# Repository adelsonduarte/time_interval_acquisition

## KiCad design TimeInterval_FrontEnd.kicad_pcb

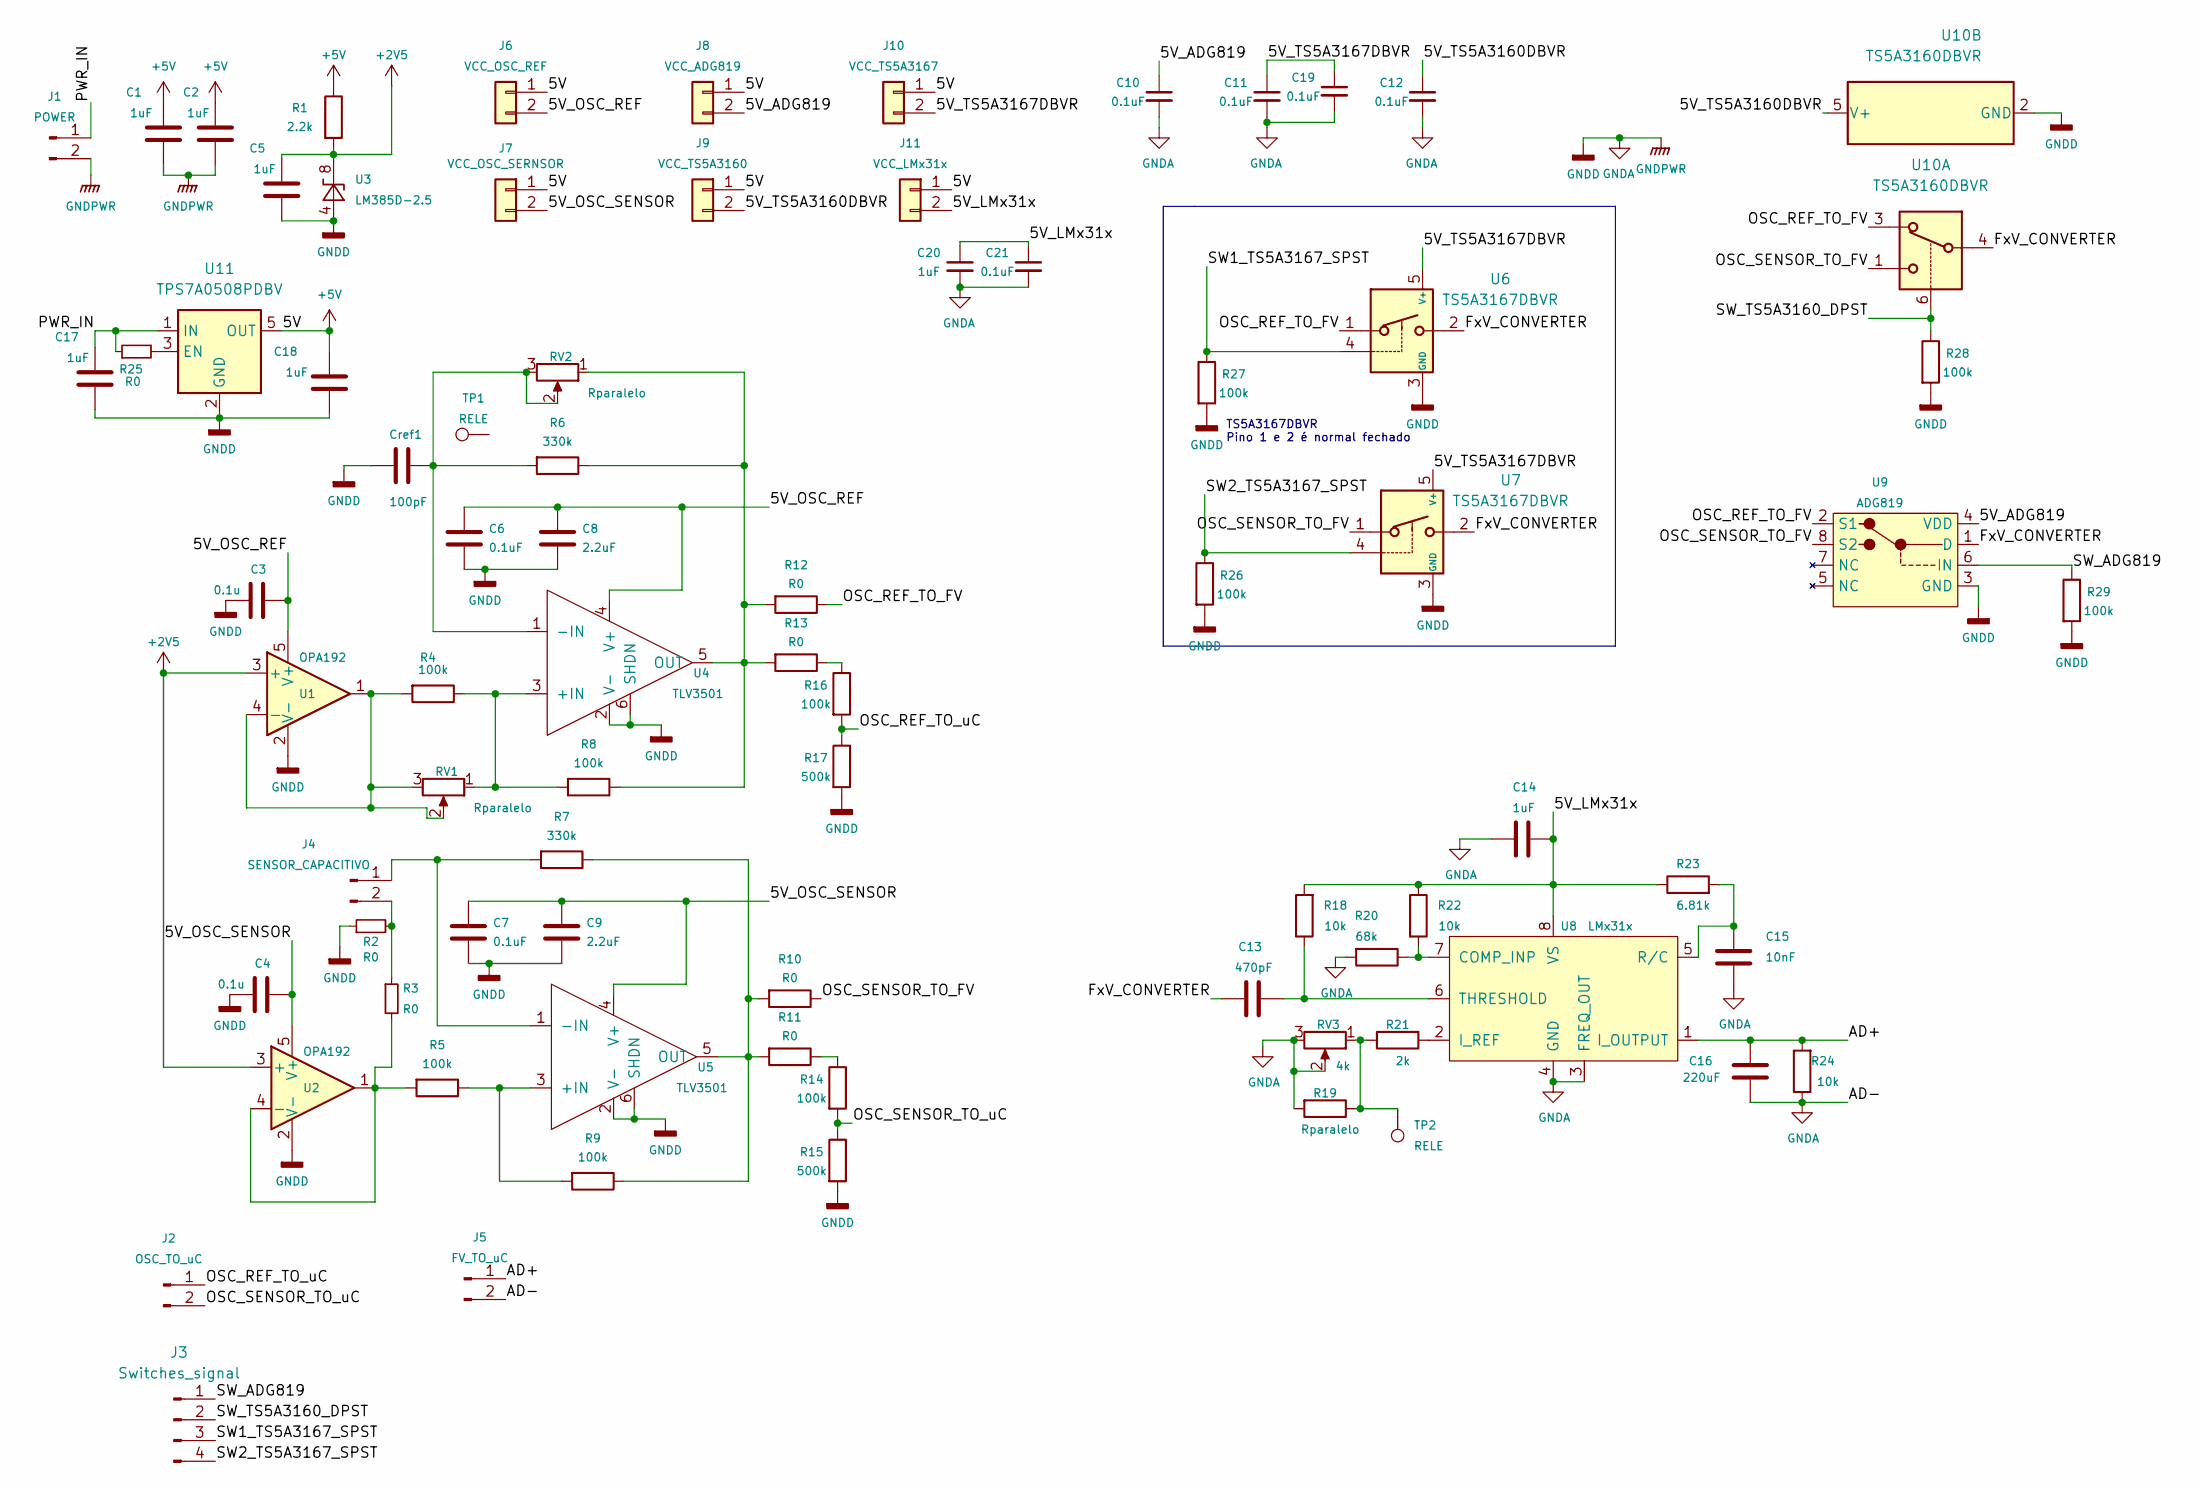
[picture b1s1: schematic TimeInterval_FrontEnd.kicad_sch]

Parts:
C1, C2, C5, C14, C17, C18, C20: 1uF; C_1206_3216Metric_Pad1.33x1.80mm_HandSolder
C3, C4: 0.1u; C_1206_3216Metric_Pad1.33x1.80mm_HandSolder
C6, C7, C10, C11, C12, C19, C21: 0.1uF; C_1206_3216Metric_Pad1.33x1.80mm_HandSolder
C8, C9: 2.2uF; C_1206_3216Metric_Pad1.33x1.80mm_HandSolder
C13: 470pF; C_1206_3216Metric_Pad1.33x1.80mm_HandSolder
C15: 10nF; C_1206_3216Metric_Pad1.33x1.80mm_HandSolder
C16: 220uF; CP_Elec_10x14.3
Cref1: 100pF; C_1206_3216Metric_Pad1.33x1.80mm_HandSolder
J1: POWER; Molex_KK-254_AE-6410-02A_1x02_P2.54mm_Vertical
J2: OSC_TO_uC; Molex_KK-254_AE-6410-02A_1x02_P2.54mm_Vertical
J3: Switches_signal; Molex_KK-254_AE-6410-04A_1x04_P2.54mm_Vertical
J4: SENSOR_CAPACITIVO; Molex_KK-254_AE-6410-02A_1x02_P2.54mm_Vertical
J5: FV_TO_uC; Molex_KK-254_AE-6410-02A_1x02_P2.54mm_Vertical
J6: VCC_OSC_REF; PinHeader_1x02_P2.54mm_Vertical
J7: VCC_OSC_SERNSOR; PinHeader_1x02_P2.54mm_Vertical
J8: VCC_ADG819; PinHeader_1x02_P2.54mm_Vertical
J9: VCC_TS5A3160; PinHeader_1x02_P2.54mm_Vertical
J10: VCC_TS5A3167; PinHeader_1x02_P2.54mm_Vertical
J11: VCC_LMx31x; PinHeader_1x02_P2.54mm_Vertical
R1: 2.2k; R_1206_3216Metric_Pad1.30x1.75mm_HandSolder
R2, R3, R10, R11, R12, R13, R25: R0; R_1206_3216Metric_Pad1.30x1.75mm_HandSolder
R4, R5, R8, R9, R14, R16, R26, R27, R28, R29: 100k; R_1206_3216Metric_Pad1.30x1.75mm_HandSolder
R6, R7: 330k; R_1206_3216Metric_Pad1.30x1.75mm_HandSolder
R15, R17: 500k; R_1206_3216Metric_Pad1.30x1.75mm_HandSolder
R18, R22, R24: 10k; R_1206_3216Metric_Pad1.30x1.75mm_HandSolder
R19: Rparalelo; R_1206_3216Metric_Pad1.30x1.75mm_HandSolder
R20: 68k; R_1206_3216Metric_Pad1.30x1.75mm_HandSolder
R21: 2k; R_1206_3216Metric_Pad1.30x1.75mm_HandSolder
R23: 6.81k; R_1206_3216Metric_Pad1.30x1.75mm_HandSolder
RV1, RV2: Rparalelo; Potentiometer_Bourns_3296W_Vertical
RV3: 4k; Potentiometer_Bourns_3296W_Vertical
TP1, TP2: RELE; TestPoint_Pad_1.0x1.0mm
U1, U2: OPA192; SOT-23-5_HandSoldering
U3: LM385D-2.5; SOIC-8_3.9x4.9mm_P1.27mm
U4, U5: TLV3501; SOT-23-6_Handsoldering
U6, U7: TS5A3167DBVR; SOT-23-5
U8: LMx31x; DIP-8_W7.62mm
U9: ADG819; MSOP-8_3x3mm_P0.65mm
U10: TS5A3160DBVR; SOT-23-6
U11: TPS7A0508PDBV; SOT-23-5

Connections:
+2V5: C5.2, R1.2, U1.3 (+), U2.3 (+), U3.8 (K)
+5V: C1.2, C2.2, C18.2, J6.1, J7.1, J8.1, J9.1, J10.1, J11.1, R1.1, U11.5 (OUT)
/5V_ADG819: C10.1, J8.2, U9.4 (VDD)
/5V_LMx31x: C14.1, C20.1, C21.1, J11.2, R18.2, R22.1, R23.1, U8.8 (VS)
/5V_OSC_REF: C3.2, C6.1, C8.1, J6.2, U1.5 (V+), U4.4 (V+)
/5V_OSC_SENSOR: C4.2, C7.1, C9.1, J7.2, U2.5 (V+), U5.4 (V+)
/5V_TS5A3160DBVR: C12.1, J9.2, U10.5 (V+)
/5V_TS5A3167DBVR: C11.1, C19.1, J10.2, U6.5 (V+), U7.5 (V+)
/AD+: C16.1, J5.1, R24.2, U8.1 (I_OUTPUT)
/FxV_CONVERTER: C13.1, U6.2, U7.2, U9.1 (D), U10.4
/OSC_REF_TO_FV: R12.1, U6.1, U9.2 (S1), U10.3
/OSC_REF_TO_uC: J2.1, R16.2, R17.1
/OSC_SENSOR_TO_FV: R10.1, U7.1, U9.8 (S2), U10.1
/OSC_SENSOR_TO_uC: J2.2, R14.2, R15.1
/PWR_IN: C17.2, J1.1, R25.1, U11.1 (IN)
/SW1_TS5A3167_SPST: J3.3, R27.1, U6.4
/SW2_TS5A3167_SPST: J3.4, R26.1, U7.4
/SW_ADG819: J3.1, R29.1, U9.6 (IN)
/SW_TS5A3160_DPST: J3.2, R28.1, U10.6
GNDA: C1.1, C2.1, C3.1, C4.1, C5.1, C6.2, C7.2, C8.2, C9.2, C10.2, C11.2, C12.2, C14.2, C15.2, C16.2, C17.1, C18.1, C19.2, C20.2, C21.2, Cref1.1, J1.2, J5.2, R2.1, R15.2, R17.2, R19.2, R20.2, R24.1, R26.2, R27.2, R28.2, R29.2, RV3.2, RV3.3, U1.2 (V-), U2.2 (V-), U3.4 (A), U4.2 (V-), U4.6 (SHDN), U5.2 (V-), U5.6 (SHDN), U6.3 (GND), U7.3 (GND), U8.3 (FREQ_OUT), U8.4 (GND), U9.3 (GND), U10.2 (GND), U11.2 (GND)
unnamed: C13.2, R18.1, U8.6 (THRESHOLD)
unnamed: C15.1, R23.2, U8.5 (R/C)
unnamed: Cref1.2, R6.2, RV2.2, RV2.3, U4.1 (-IN)
unnamed: J4.1, R7.2, U5.1 (-IN)
unnamed: J4.2, R2.2, R3.1
unnamed: R3.2, R5.2, U2.1, U2.4 (-)
unnamed: R4.1, R8.2, RV1.1, U4.3 (+IN)
unnamed: R4.2, RV1.2, RV1.3, U1.1, U1.4 (-)
unnamed: R5.1, R9.2, U5.3 (+IN)
unnamed: R7.1, R9.1, R10.2, R11.2, U5.5 (OUT)
unnamed: R11.1, R14.1
unnamed: R6.1, R8.1, R12.2, R13.2, RV2.1, U4.5 (OUT)
unnamed: R13.1, R16.1
unnamed: R19.1, R21.2, RV3.1, TP2.1
unnamed: R20.1, R22.2, U8.7 (COMP_INP)
unnamed: R21.1, U8.2 (I_REF)
unnamed: R25.2, U11.3 (EN)

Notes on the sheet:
TS5A3167DBVR Pino 1 e 2 é normal fechado

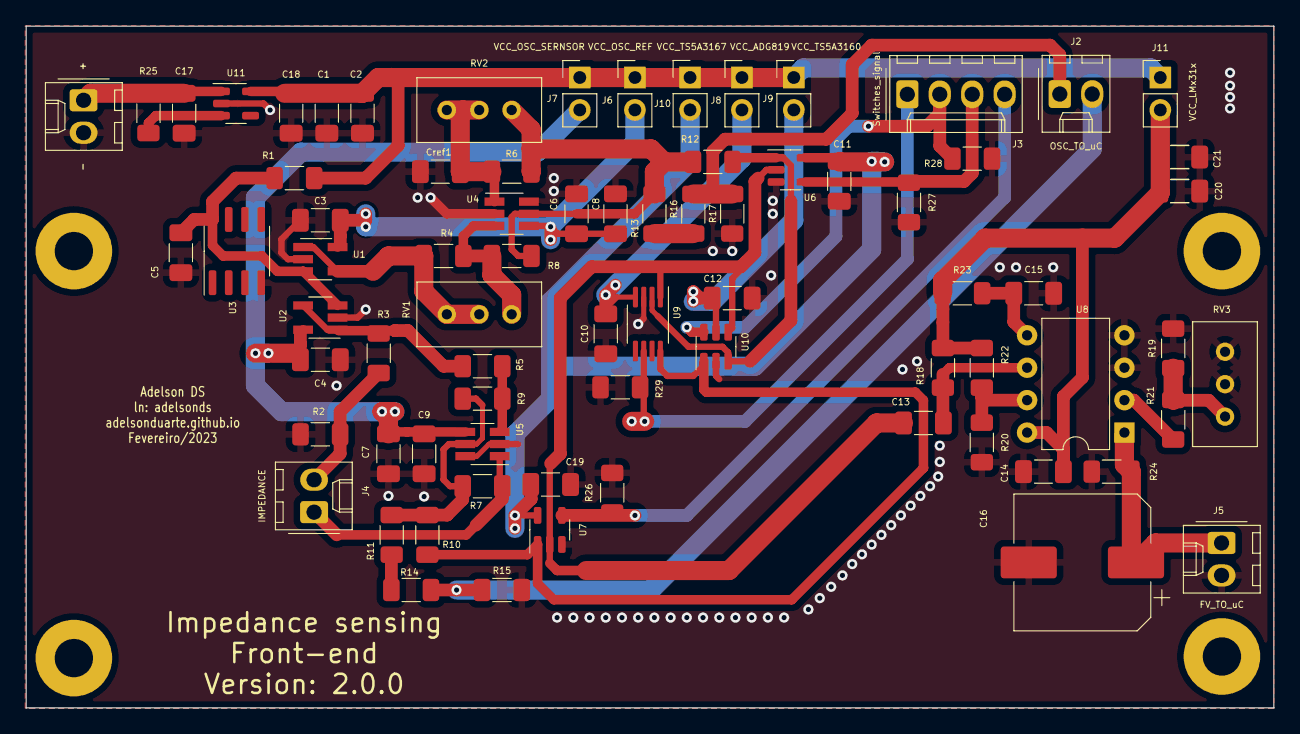
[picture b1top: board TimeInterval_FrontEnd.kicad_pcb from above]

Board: 2 copper layers, 97.7 x 53.4 mm, 76 parts (0 on the bottom side), 37 nets.

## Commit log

2023-02-20 Start design
